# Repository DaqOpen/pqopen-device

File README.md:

# pqopen-device

**pqopen-device** is a cost-effective, open-source measurement device for monitoring voltage and current within electrical distribution panels. It includes power quality (PQ) functionalities compliant with **IEC 61000-4-30** and is designed for tech enthusiasts and educational institutions. It bases on the [daqopen-lib](https://github.com/DaqOpen/daqopen-lib) for  data acquisition and [pqopen-lib](https://github.com/DaqOpen/pqopen-lib) for the power quality processing part.

> [!WARNING] 
> The actual hardware design is not tested so far. Please wait until an official release.

## Key Features

- **Voltage Measurement**: Measure and analyze 3-phase mains voltage up to 330 VAC
- **Current Measurement**: Use clamps like SCT13-0000 for current measurement
- **Power Quality**: Analysis of RMS, Harmonics, Interharmonics, Flicker and more according to IEC 61000-4-30
- **Data Aggregation**: Use different storage intervals for logging selected parameters to CSV or MQTT
- **Cost-Effective**: Built using open-source hardware like the **Arduino Due** and **Raspberry Pi**.

## Target Audience

- **Tech Enthusiasts**: People interested in measurement technology and electrical energy supply.
- **Educational Institutions**: For training and research purposes.

## Hardware Overview

The device comprises:

- A custom **mainboard** with connectors, power supplies, and signal conditioning for voltage and current.
- **Arduino Due** for data acquisition (running with 55 kS/s per channel)
- **Raspberry Pi 3A+** as the edge device.
- A **standard DIN-rail enclosure** (9 module width).

The main pcb is dual layer with components on both sides. It uses typically SMT components with down to size of 0805 to be soldered by hand.

## Software Overview

The software is split into several components:

### Firmware for Arduino Due

Runs on the Arduino Due for ADC data acquisition (see https://github.com/DaqOpen/daqopen-lib)

Written in C++ for Arduino IDE

### Software for Raspberry Pi

There are three main software components running on the Raspberry Pi edge device to fulfill the measurement needs:

#### daqopen-zmq-server.py

This is the data entry point for the further processing. It receives data form the Arduino Due, adds timestamps as well as channel properties and provides the data via a ZMQ PUB/SUB interface.

This service is time critical due to limited buffer on the Arduino Due and is therefore started with higher priority and realtime scheduler option.

#### pqopen.py

The pqopen app is the main processing application. It connects to the daqopen-zmq-server and receives the data, calculates power values and outputs it on the configured interfaces.

#### persistmq-bridge.py

When data loss is no option, the persistmq-bridge helps to cache data in case of connection loss and resending capability.

## Platform Compatibility

- **Core Library**: Runs on ARM64, AMD64, Linux, and Windows (Mac compatibility untested).
- **Main Application**: Designed specifically for the Raspberry Pi.

## Installation

An **initial setup guide** will be provided to assist with assembling the hardware and installing the software soon.

## Documentation

Documentation for the overarching project is available at [docs.daqopen.com](https://docs.daqopen.com). This documentation will be expanded to include specifics for pqopen-device.

## Contribution

Contributions are welcome, provided they align with the project's vision. Feel free to open issues, submit pull requests, or engage in discussions.

## License

This project is licensed under the **MIT License**.

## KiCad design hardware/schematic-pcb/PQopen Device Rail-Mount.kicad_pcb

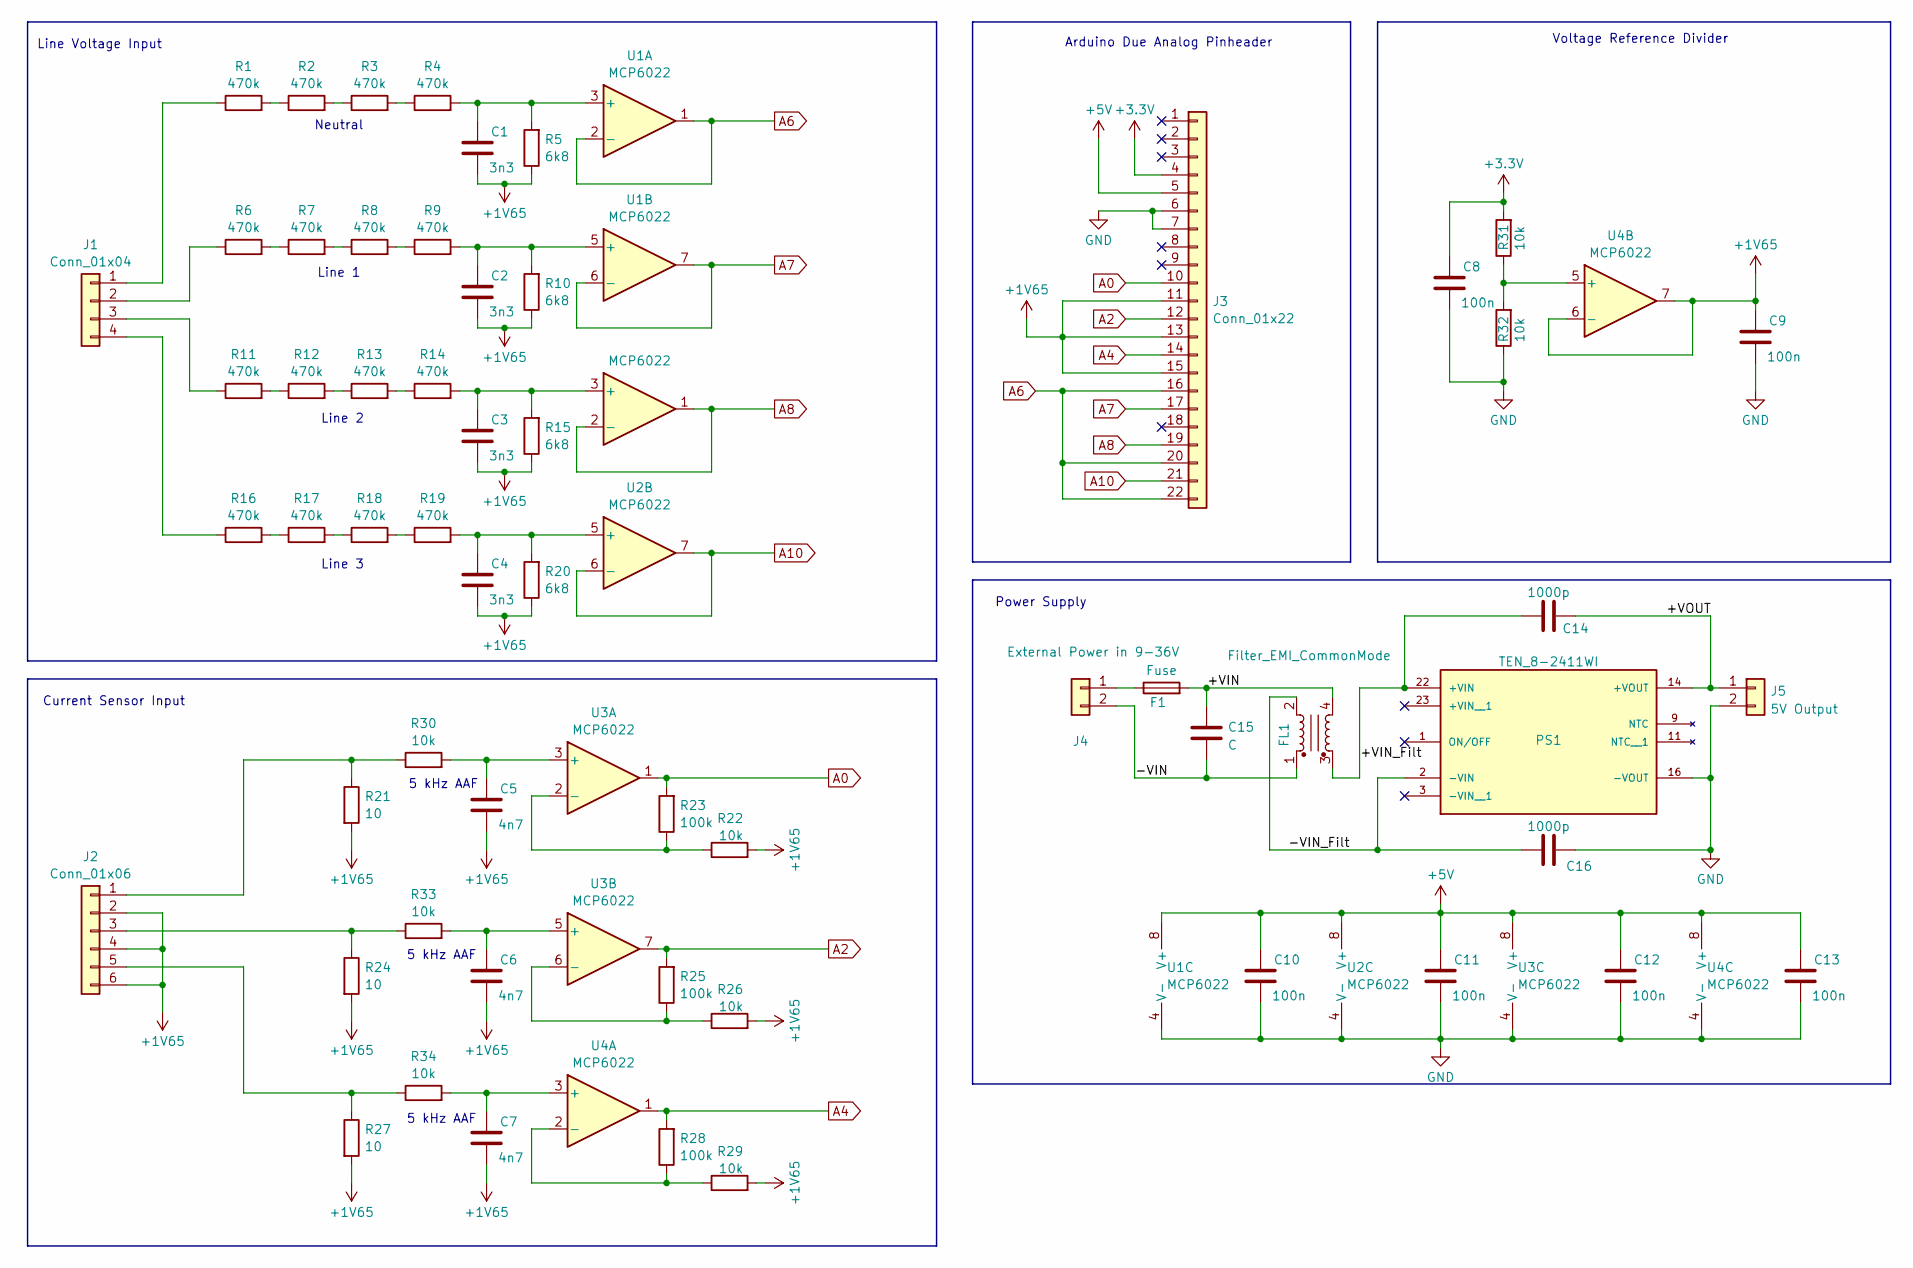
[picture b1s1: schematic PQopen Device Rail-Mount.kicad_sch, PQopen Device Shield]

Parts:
C1, C2, C3, C4: 3n3; C_0805_2012Metric
C5, C6, C7: 4n7; C_0805_2012Metric
C8, C9, C10, C11, C12, C13: 100n; C_0805_2012Metric
C14, C16: 1000p; C_1206_3216Metric_Pad1.33x1.80mm_HandSolder; Part Number 1206GC102KAT1A
C15: C; C_1812_4532Metric_Pad1.57x3.40mm_HandSolder; Part Number C1812F475K5RACTU
F1: Fuse; Fuse_Littelfuse_372_D8.50mm
FL1: Filter_EMI_CommonMode; TCK050
J1: Conn_01x04; PhoenixContact_GMSTB_2,5_4-GF-7,62_1x04_P7.62mm_Horizontal_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
J2: Conn_01x06; PhoenixContact_MSTB_2,5_6-GF-5,08_1x06_P5.08mm_Horizontal_T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
J3: Conn_01x22; PinHeader_1x22_P2.54mm_Vertical
J4: External Power in 9-36V; PhoenixContact_MSTB_2,5_2-GF-5,08_1x02_P5.08mm_Horizontal_T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
J5: 5V Output; PinHeader_1x02_P2.54mm_Vertical
PS1: TEN_8-2411WI; CONV_TEN_8-2411WI; PARTREV September 29, 2020
R1, R2, R3, R4, R6, R7, R8, R9, R11, R12, R13, R14, R16, R17, R18, R19: 470k; R_1206_3216Metric
R5, R10, R15, R20: 6k8; R_0805_2012Metric
R21, R24, R27: 10; R_0805_2012Metric
R22, R26, R29, R30, R31, R32, R33, R34: 10k; R_0805_2012Metric
R23, R25, R28: 100k; R_0805_2012Metric
U1, U2, U3, U4: MCP6022; SOIC-8_3.9x4.9mm_P1.27mm

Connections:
+1V65: C1.2, C2.2, C3.2, C4.2, C5.2, C6.2, C7.2, C9.1, J2.2, J2.4, J2.6, J3.11, J3.13, J3.15, R5.1, R10.1, R15.1, R20.1, R21.2, R22.2, R24.2, R26.2, R27.2, R29.2, U4.6 (-), U4.7
+3.3V: C8.1, J3.4, R31.2
+5V: C10.1, C11.1, C12.1, C13.1, J3.5, U1.8 (V+), U2.8 (V+), U3.8 (V+), U4.8 (V+)
/+VIN: C15.1, F1.2, FL1.4
/+VIN_Filt: C14.1, FL1.3, PS1.22 (+VIN)
/+VOUT: C14.2, J5.1, PS1.14 (+VOUT)
/-VIN: C15.2, FL1.1, J4.2
/-VIN_Filt: C16.1, FL1.2, PS1.2 (-VIN)
A0: J3.10, R23.2, U3.1
A2: J3.12, R25.2, U3.7
A4: J3.14, R28.2, U4.1
A6: J3.16, J3.20, J3.22, U1.1, U1.2 (-)
A7: J3.17, U1.6 (-), U1.7
A8: J3.19, U2.1, U2.2 (-)
A10: J3.21, U2.6 (-), U2.7
GND: C8.2, C9.2, C10.2, C11.2, C12.2, C13.2, C16.2, J3.6, J3.7, J5.2, PS1.16 (-VOUT), R32.1, U1.4 (V-), U2.4 (V-), U3.4 (V-), U4.4 (V-)
unnamed: J1.1, R1.1
unnamed: J1.2, R6.1
unnamed: J1.3, R11.1
unnamed: J1.4, R16.1
unnamed: J2.1, R21.1, R30.1
unnamed: J2.3, R24.1, R33.1
unnamed: J2.5, R27.1, R34.1
unnamed: F1.1, J4.1
unnamed: R1.2, R2.1
unnamed: R2.2, R3.1
unnamed: R3.2, R4.1
unnamed: R6.2, R7.1
unnamed: R7.2, R8.1
unnamed: R8.2, R9.1
unnamed: R11.2, R12.1
unnamed: R12.2, R13.1
unnamed: R13.2, R14.1
unnamed: R16.2, R17.1
unnamed: R17.2, R18.1
unnamed: R18.2, R19.1
unnamed: C1.1, R4.2, R5.2, U1.3 (+)
unnamed: C2.1, R9.2, R10.2, U1.5 (+)
unnamed: C3.1, R14.2, R15.2, U2.3 (+)
unnamed: C4.1, R19.2, R20.2, U2.5 (+)
unnamed: C5.1, R30.2, U3.3 (+)
unnamed: R22.1, R23.1, U3.2 (-)
unnamed: C6.1, R33.2, U3.5 (+)
unnamed: R25.1, R26.1, U3.6 (-)
unnamed: C7.1, R34.2, U4.3 (+)
unnamed: R28.1, R29.1, U4.2 (-)
unnamed: R31.1, R32.2, U4.5 (+)

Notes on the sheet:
Neutral
5 kHz AAF
Line 3
Line Voltage Input
Line 1
Voltage Reference Divider
Current Sensor Input
Arduino Due Analog Pinheader
Power Supply
Line 2

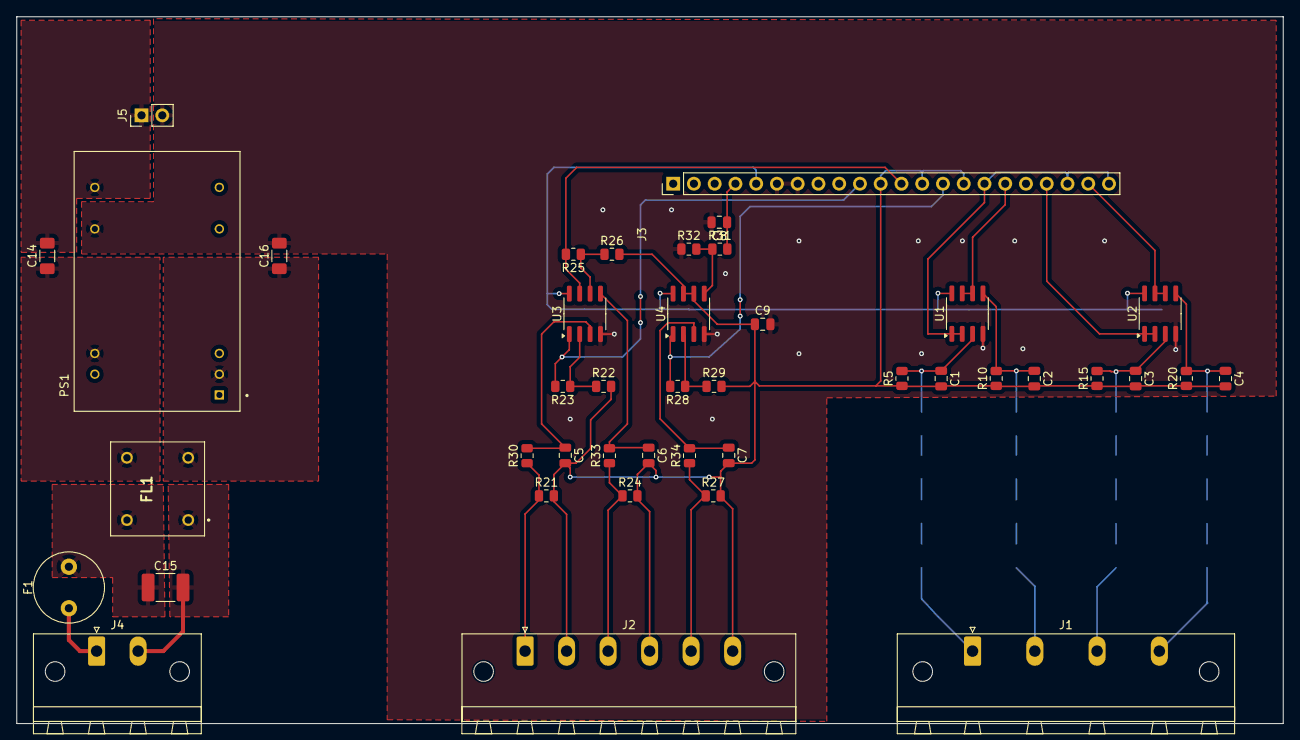
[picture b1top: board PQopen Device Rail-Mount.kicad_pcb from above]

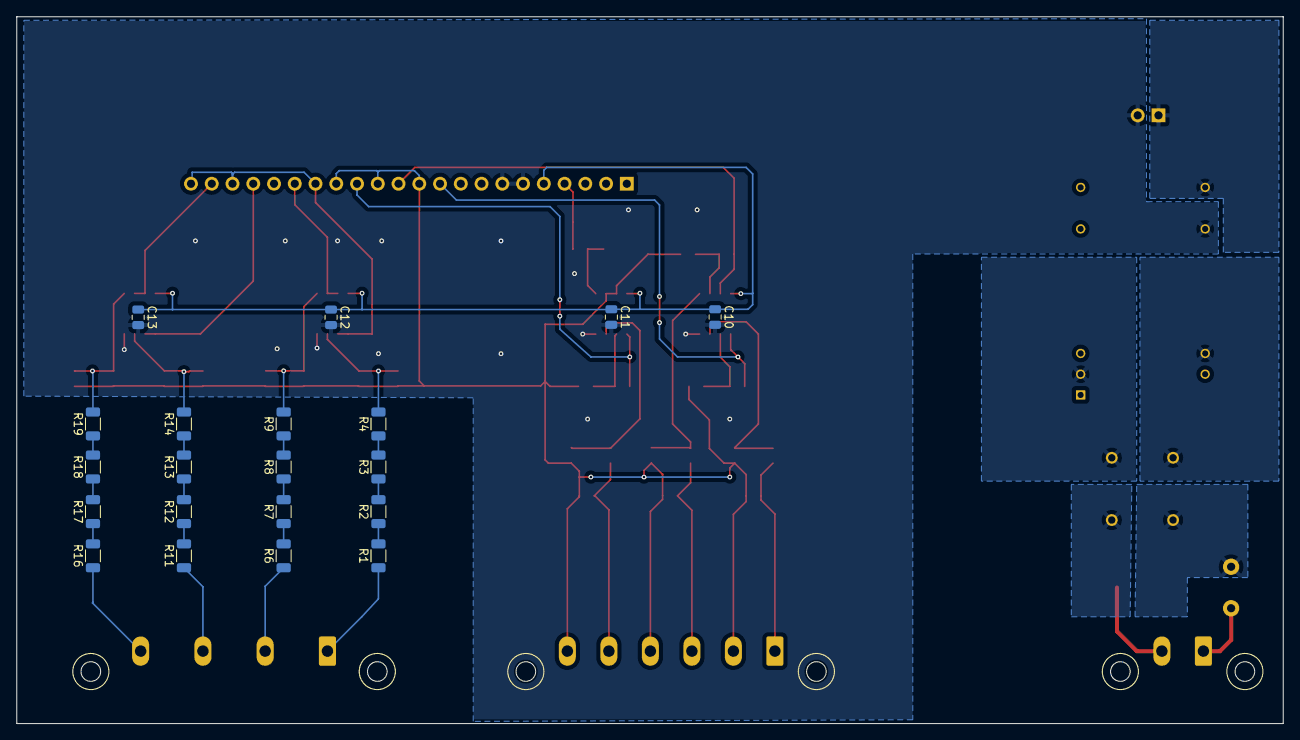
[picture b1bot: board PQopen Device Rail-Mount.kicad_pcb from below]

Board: 2 copper layers, 155.0 x 86.5 mm, 62 parts (20 on the bottom side), 47 nets.

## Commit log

2024-12-22 hardware: initial commit of schematic and draft of pcb
2024-12-23 update of README
2025-01-02 hardware: minor improvements
2025-01-06 apps: initially added main apps
2025-01-06 installation: added initial version of installation script
2025-01-20 pqopen-app: reduced num-threads to 1; increase acq sample buffer to 200_000
2025-01-21 daqzmq-server: cleanup
2025-02-07 fixed problem reading device_id; tie daqopen process to CPU in unit file
2025-02-21 mqtt-bridge: initial commit
2025-03-06 added persistmq to installer
2025-03-08 added comitup to install script
2025-04-12 added new features from pqopen-lib.
2025-05-10 configuration: inline comments for config files
2025-05-10 docs: added initial documentation
2025-05-10 config & docs: some fixes
2025-05-19 persistmq-bridge: allow secure tls connection
2025-05-19 persistmq-bridge: allow secure tls connection - added missing file
2025-06-04 persistmq-bridge: added option for multi message (bulk) transfer
2025-06-04 docs: added assembly instructions
2025-06-07 added status reporter to apps
2025-06-11 pqopen-app: fix breaking after timeout; only init eventdetector if entry in config
2025-06-11 pqopen-app: added missing channel update()
2025-06-12 status-app: use udp for status communication
2025-06-12 install-script: added status monitor
2025-06-12 statuscomm: fixed typing and logging config
2025-06-13 config: modified default config
2025-06-19 status-monitor: change to active high
2025-06-19 status-monitor: fixed typo; persistmq: gently stop workers
2025-06-19 time_sync: avoid running of acquisition if system time is not synced
2025-06-19 time_sync: added missing file
2025-06-20 status-monitor: try to blink with about 1Hz
2025-06-20 status-monitor: also enable blinking on yellow led
2025-06-22 Update install.sh
    Added creation of cache directory
2025-07-25 zmq-server: adapted time sync mechanism for smoother control
2025-07-26 zmq-server: alternative time sync control loop
2025-07-27 zmq-server: another alternative time sync control loop
2025-08-06 daq-zmq-server: correction of timestamp with board property adc_delay_seconds
2025-08-21 daq-zmq-server: adaption of time sync mechanism to avoid swinging at the beginning
2025-08-25 pqopen-app: added optional feature one_period_fundamental
2025-11-27 daqopen-zmq-server: alternative time-sync mechanism
2025-12-04 pqopen-app: added support for 3P3W measurement via N-L2 and N-L3 ; additional config options
2025-12-23 pqopen-app: added support for storing measurement config to storage endpoints
2026-02-01 daq-zmq-server: don't quit in case of packet jitter, just write warning.
